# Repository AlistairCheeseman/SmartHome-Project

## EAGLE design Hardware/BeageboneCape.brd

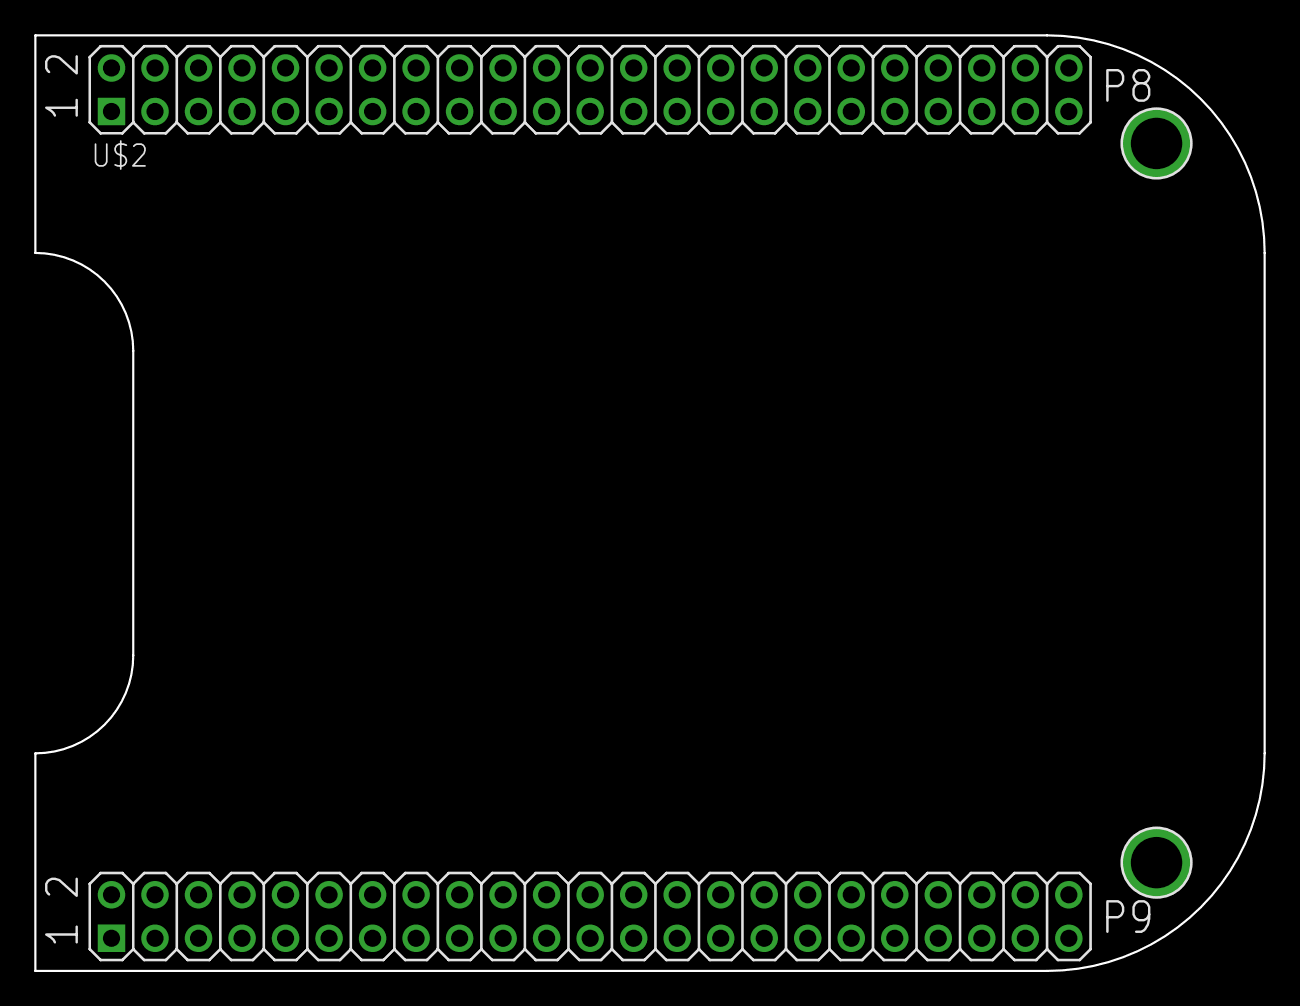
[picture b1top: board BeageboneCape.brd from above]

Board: 2 copper layers, 71.8 x 54.6 mm, 3 parts (0 on the bottom side), 4 nets, no tracks yet.

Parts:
U$2: BEAGLEBONE_OUTLINE; BEAGLEBONE_SHIELD
U$22, U$23: MOUNTINGHOLE3.0THIN; MOUNTINGHOLE_3.0_PLATEDTHIN

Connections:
3.3V: U$2.49, U$2.50
5.0V: U$2.53, U$2.54
GND: U$2.1, U$2.2, U$2.47, U$2.48, U$2.89, U$2.90, U$2.91, U$2.92
VDD_5V: U$2.51, U$2.52

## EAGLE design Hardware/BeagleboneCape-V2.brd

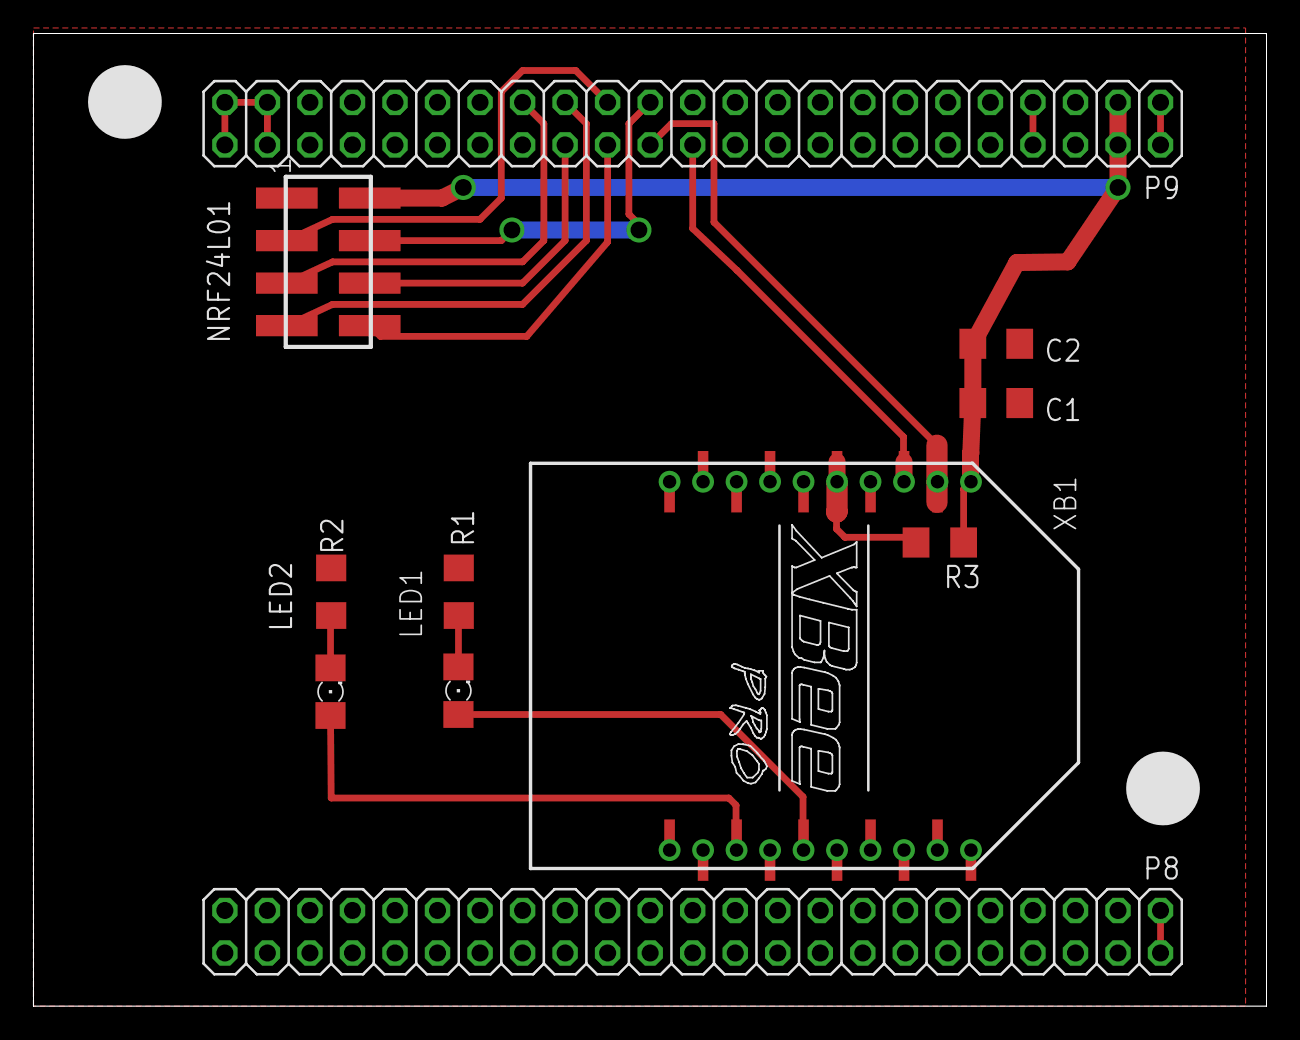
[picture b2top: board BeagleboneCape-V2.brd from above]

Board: 2 copper layers, 73.6 x 58.1 mm, 11 parts (0 on the bottom side), 16 nets.

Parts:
C1: 1u; C1206
C2: 8.2p; C1206
LED1: Assoc; 1206
LED2: ON_SLEEP; 1206
NRF24L01: NRF1; TSM-110-XX-XXX-DV
P8: HEADER1; 2X23
P9: HEADER2; 2X23
R1, R2, R3: 110R; R1206
XB1: XBEE-PRO

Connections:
3.3V: C1.1, C2.1, NRF24L01.2, P9.3, P9.4, R3.1, XB1.1, XB1.1-1
5.0V: P9.7, P9.8
ASSOC: LED1.A, XB1.15, XB1.15-1
BB_RX: P9.26, XB1.2, XB1.2-1
BB_TX: P9.24, XB1.3, XB1.3-1
CE: NRF24L01.3, P9.27
CSN: NRF24L01.4, P9.25
GND: C1.2, C2.2, NRF24L01.1, P8.1, P8.2, P9.1, P9.2, P9.43, P9.44, P9.45, P9.46, R1.1, R2.1, XB1.10, XB1.10-1, XB1.14, XB1.14-1
IRQ: NRF24L01.8, P9.28
MISO: NRF24L01.7, P9.29
MOSI: NRF24L01.6, P9.30
unnamed: LED1.C, R1.2
unnamed: R3.2, XB1.5, XB1.5-1
unnamed: LED2.C, R2.2
ON_SLEEP: LED2.A, XB1.13, XB1.13-1
SCK: NRF24L01.5, P9.31

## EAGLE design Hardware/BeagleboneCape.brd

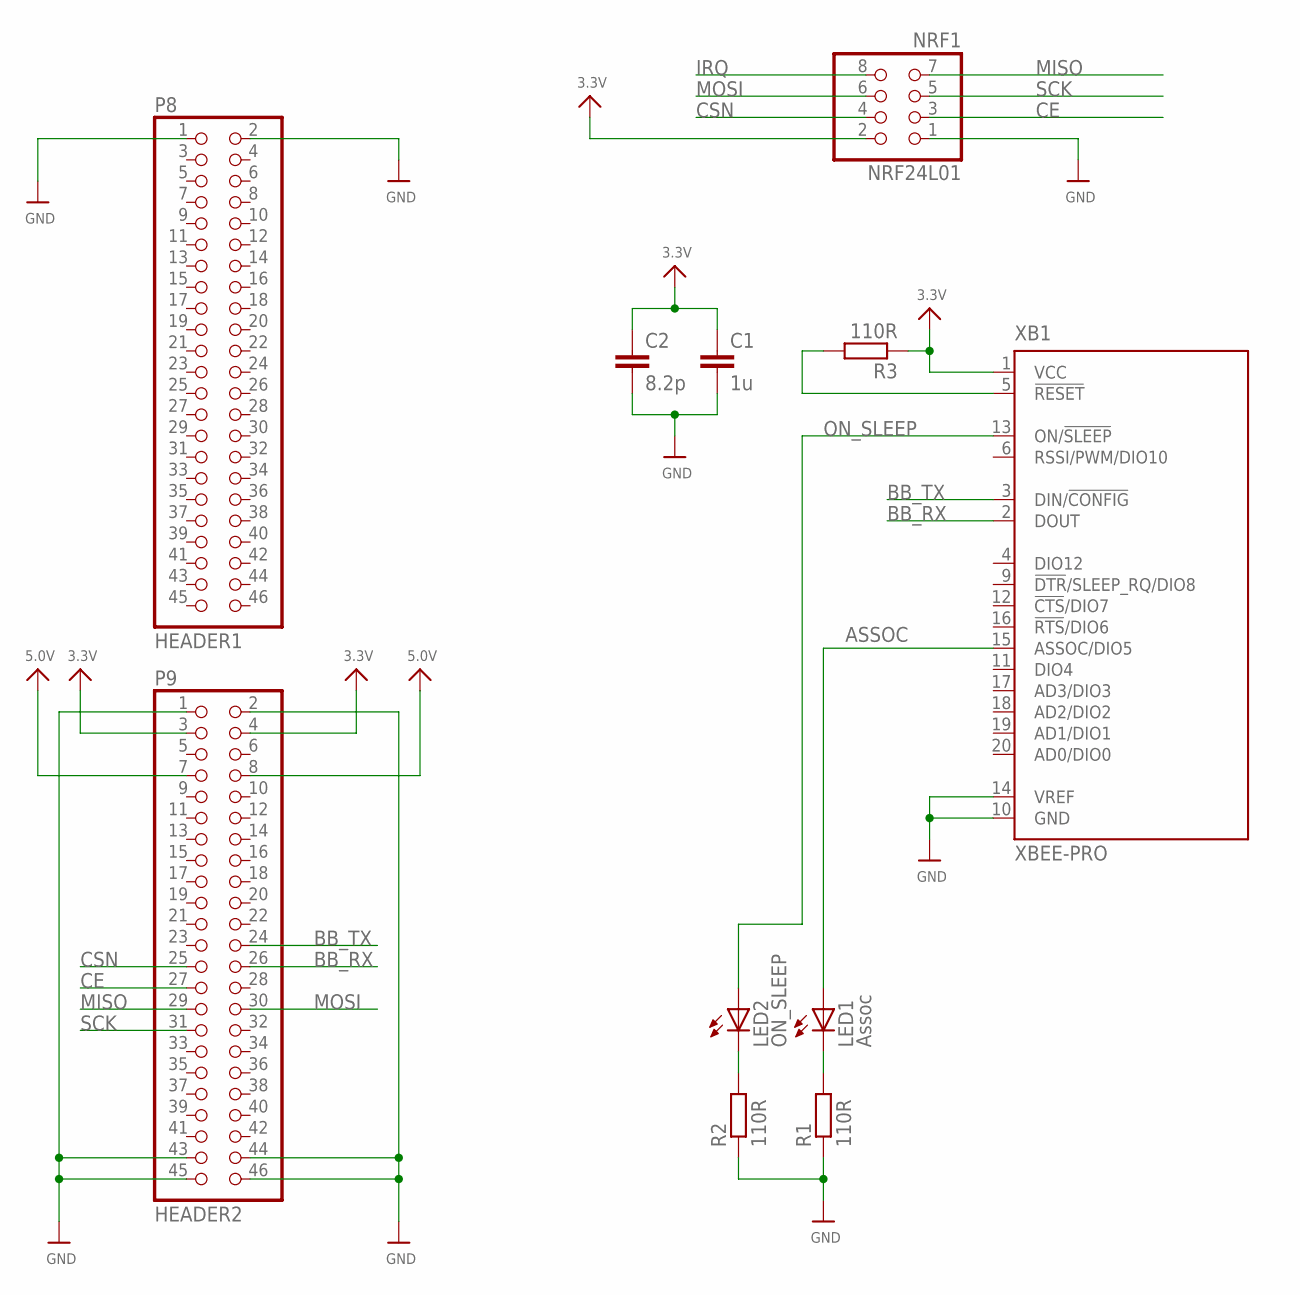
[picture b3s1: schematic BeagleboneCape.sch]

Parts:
C1: 1u; C025-025X050
C2: 8.2p; C025-025X050
LED1: Assoc; LED5MM
LED2: ON_SLEEP; LED5MM
NRF24L01: NRF1; 2X04
P8: HEADER1; 2X23
P9: HEADER2; 2X23
R1, R2, R3: 110R; 0207/7
XB1: XBEE-PRO

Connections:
3.3V: C1.1, C2.1, NRF24L01.2, P9.3, P9.4, R3.1, XB1.1 (VCC)
5.0V: P9.7, P9.8
ASSOC: LED1.A, XB1.15 (ASSOC/DIO5)
BB_RX: P9.26, XB1.2 (DOUT)
BB_TX: P9.24, XB1.3 (DIN/!CONFIG)
CE: NRF24L01.3, P9.27
CSN: NRF24L01.4, P9.25
GND: C1.2, C2.2, NRF24L01.1, P8.1, P8.2, P9.1, P9.2, P9.43, P9.44, P9.45, P9.46, R1.1, R2.1, XB1.10 (GND), XB1.14 (VREF)
IRQ: NRF24L01.8
MISO: NRF24L01.7, P9.29
MOSI: NRF24L01.6, P9.30
unnamed: LED1.K (C), R1.2
unnamed: R3.2, XB1.5 (!RESET)
unnamed: LED2.K (C), R2.2
ON_SLEEP: LED2.A, XB1.13 (ON/!SLEEP)
SCK: NRF24L01.5, P9.31

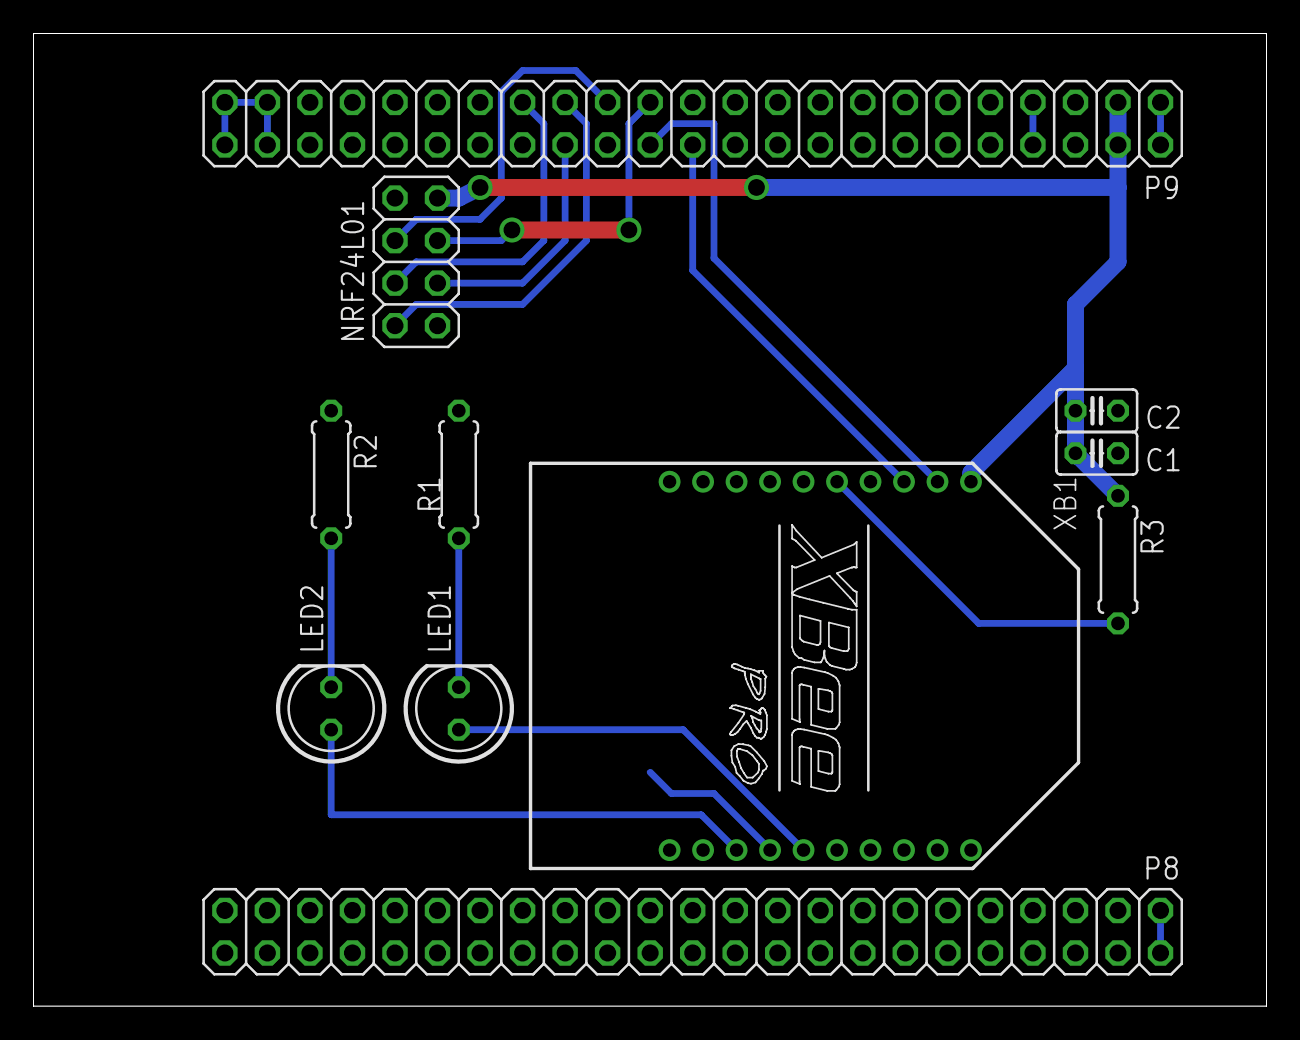
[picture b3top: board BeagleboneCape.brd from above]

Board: 2 copper layers, 73.6 x 58.1 mm, 11 parts (0 on the bottom side), 15 nets.

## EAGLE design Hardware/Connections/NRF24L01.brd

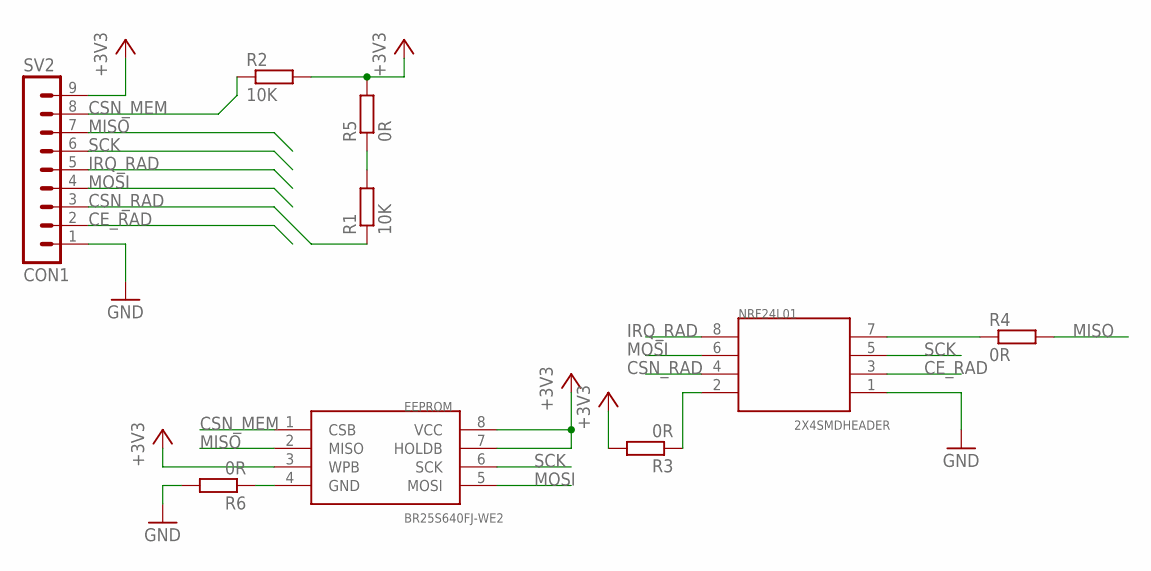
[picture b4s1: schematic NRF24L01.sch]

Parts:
EEPROM: BR25S640FJ-WE2; SO8
NRF24L01: 2X4SMDHEADER; TSM-110-XX-XXX-DV
R1, R2: 10K; R1206
R3, R4, R5, R6: 0R; R1206
SV2: CON1; MA09-1W

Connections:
+3V3: EEPROM.3 (WPB), EEPROM.7 (HOLDB), EEPROM.8 (VCC), R2.2, R3.2, R5.2, SV2.9
CE_RAD: NRF24L01.3, SV2.2
CSN_MEM: EEPROM.1 (CSB), R2.1, SV2.8
CSN_RAD: NRF24L01.4, R1.1, SV2.3
GND: NRF24L01.1, R6.2, SV2.1
IRQ_RAD: NRF24L01.8, SV2.5
MISO: EEPROM.2 (MISO), R4.2, SV2.7
MOSI: EEPROM.5 (MOSI), NRF24L01.6, SV2.4
unnamed: NRF24L01.2, R3.1
unnamed: NRF24L01.7, R4.1
unnamed: R1.2, R5.1
unnamed: EEPROM.4 (GND), R6.1
SCK: EEPROM.6 (SCK), NRF24L01.5, SV2.6

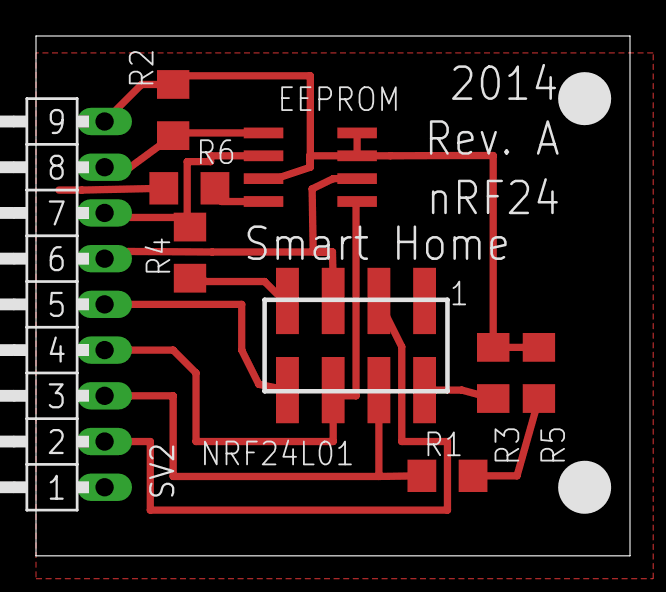
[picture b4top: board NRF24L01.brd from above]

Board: 2 copper layers, 33.0 x 28.9 mm, 9 parts (0 on the bottom side), 13 nets.

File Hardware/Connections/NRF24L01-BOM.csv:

"Qty";"Value";"Device";"Package";"Parts";"Description";"MF";"MPN";"OC_FARNELL";"OC_NEWARK";
"4";"0R";"R-EU_R1206";"R1206";"R3, R4, R5, R6";"RESISTOR, European symbol";"";"";"";"";
"2";"10K";"R-EU_R1206";"R1206";"R1, R2";"RESISTOR, European symbol";"";"";"";"";
"1";"2X4SMDHEADER";"2X4SMDHEADER";"TSM-110-XX-XXX-DV";"U$1";"";"";"";"";"";
"1";"BR25S640FJ-WE2";"BR25S640FJ-WE2";"SO8";"EEPROM";"";"";"";"";"";
"1";"CON1";"MA09-1W";"MA09-1W";"SV2";"PIN HEADER";"";"";"unknown";"unknown";

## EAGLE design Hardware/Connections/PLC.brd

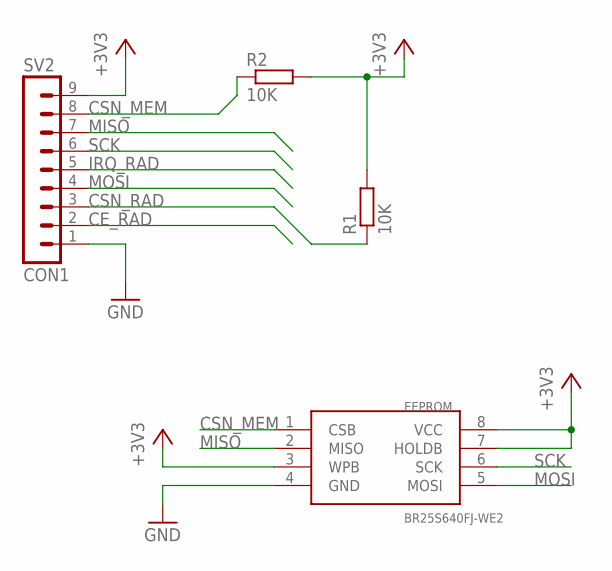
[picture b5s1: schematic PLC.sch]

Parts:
EEPROM: BR25S640FJ-WE2; SO8
R1, R2: 10K; R1206
SV2: CON1; MA09-1W

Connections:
+3V3: EEPROM.3 (WPB), EEPROM.7 (HOLDB), EEPROM.8 (VCC), R1.2, R2.2, SV2.9
CE_RAD: SV2.2
CSN_MEM: EEPROM.1 (CSB), R2.1, SV2.8
CSN_RAD: R1.1, SV2.3
GND: EEPROM.4 (GND), SV2.1
IRQ_RAD: SV2.5
MISO: EEPROM.2 (MISO), SV2.7
MOSI: EEPROM.5 (MOSI), SV2.4
SCK: EEPROM.6 (SCK), SV2.6

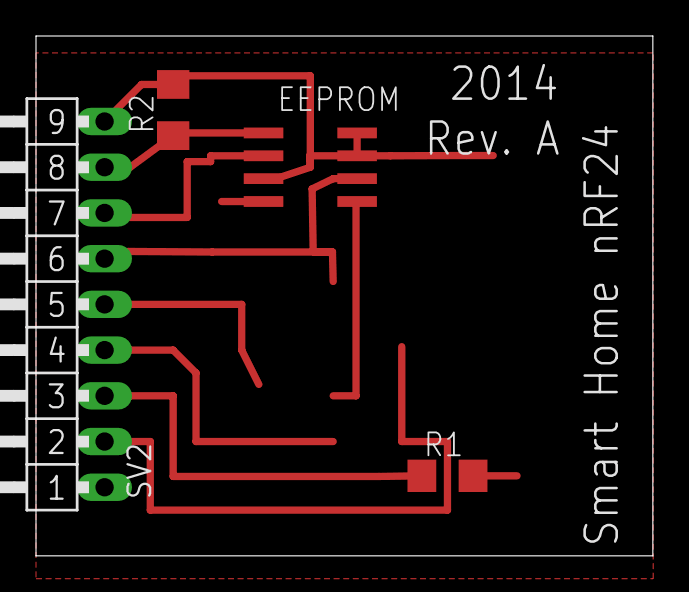
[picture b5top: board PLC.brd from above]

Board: 2 copper layers, 34.3 x 28.9 mm, 4 parts (0 on the bottom side), 7 nets.

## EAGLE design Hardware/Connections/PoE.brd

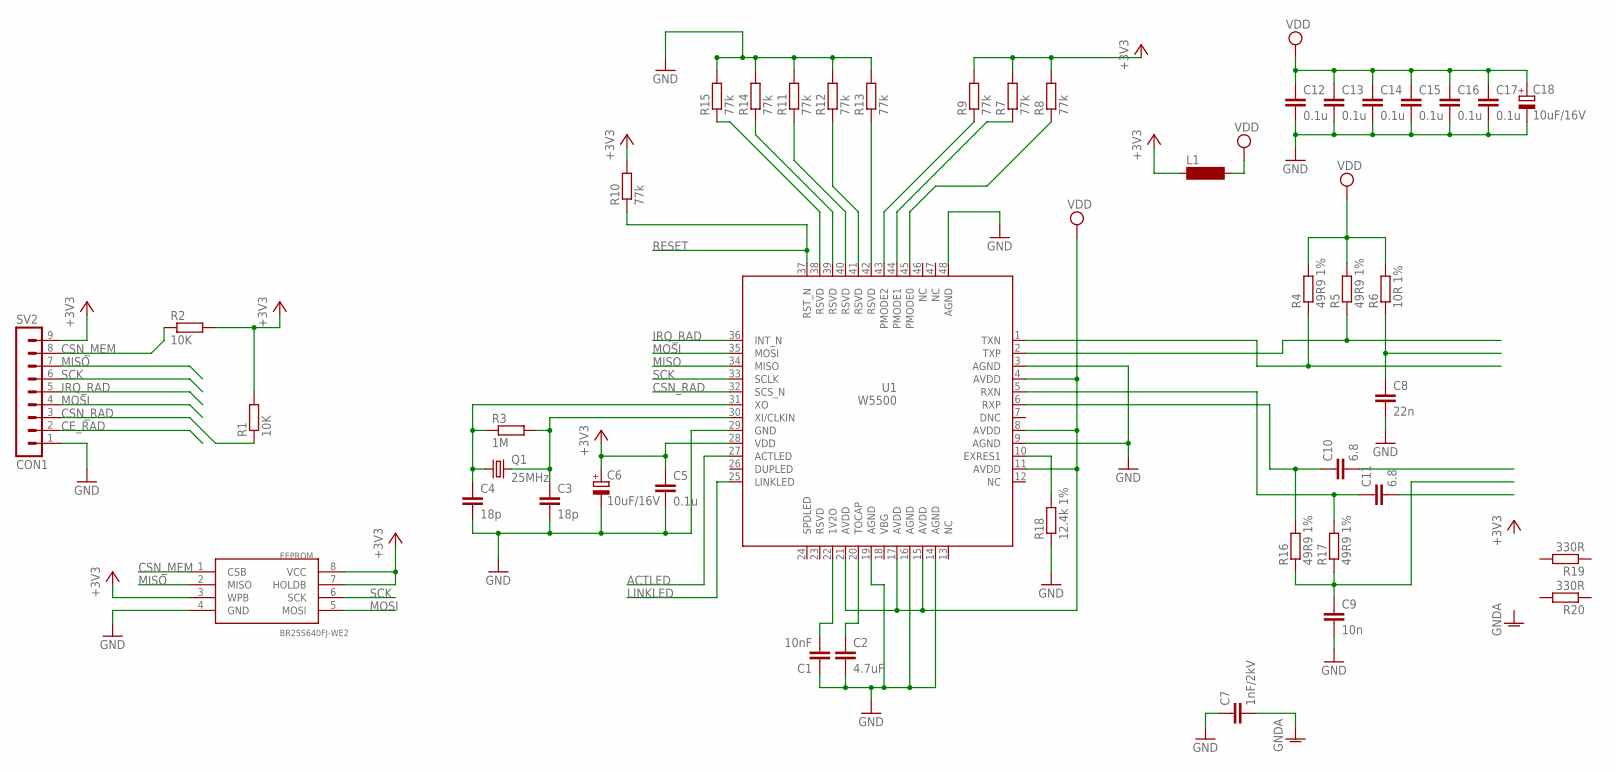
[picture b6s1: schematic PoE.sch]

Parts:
C1: 10nF; C1206
C2: 4.7uF; C1206
C3, C4: 18p; C1206
C5, C12, C13, C14, C15, C16, C17: 0.1u; C1206
C6: 10uF/16V; 153CLV-0505
C7: 1nF/2kV; C1206
C8: 22n; C1206
C9: 10n; C1206
C10, C11: 6.8; C1206
C18: 10uF/16V; 153CLV-0405
EEPROM: BR25S640FJ-WE2; SO8
L1: MS50
Q1: 25MHz; HC49UP
R1, R2: 10K; R1206
R3: 1M; R1206
R4, R5, R16, R17: 49R9 1%; R1206
R6: 10R 1%; R1206
R7, R8, R9, R10, R11, R12, R13, R14, R15: 77k; R1206
R18: 12.4k 1%; R1206
R19, R20: 330R; R1206
SV2: CON1; MA09-1W
U1: W5500

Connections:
+3V3: C5.1, C6.+, EEPROM.3 (WPB), EEPROM.7 (HOLDB), EEPROM.8 (VCC), L1.1, R1.2, R2.2, R7.2, R8.2, R9.2, R10.2, SV2.9, U1.28 (VDD)
ACTLED: U1.27 (ACTLED)
CE_RAD: SV2.2
CSN_MEM: EEPROM.1 (CSB), R2.1, SV2.8
CSN_RAD: R1.1, SV2.3, U1.32 (SCS_N)
GND: C1.1, C2.2, C3.2, C4.2, C5.2, C6.-, C7.1, C8.2, C9.2, C12.2, C13.2, C14.2, C15.2, C16.2, C17.2, C18.-, EEPROM.4 (GND), R11.2, R12.2, R13.2, R14.2, R15.2, R18.1, SV2.1, U1.3 (AGND), U1.9 (AGND), U1.14 (AGND), U1.16 (AGND), U1.19 (AGND), U1.29 (GND), U1.48 (AGND)
GNDA: C7.2
IRQ_RAD: SV2.5, U1.36 (INT_N)
LINKLED: U1.25 (LINKLED)
MISO: EEPROM.2 (MISO), SV2.7, U1.34 (MISO)
MOSI: EEPROM.5 (MOSI), SV2.4, U1.35 (MOSI)
unnamed: R9.1, U1.43 (PMODE2)
unnamed: C1.2, U1.22 (1V2O)
unnamed: C2.1, U1.20 (TOCAP)
unnamed: C4.1, Q1.1, R3.1, U1.31 (XO)
unnamed: C3.1, Q1.2, R3.2, U1.30 (XI/CLKIN)
unnamed: R7.1, U1.44 (PMODE1)
unnamed: C11.1, R17.2, U1.5 (RXN)
unnamed: R8.1, U1.45 (PMODE0)
unnamed: R15.1, U1.38 (RSVD)
unnamed: R14.1, U1.39 (RSVD)
unnamed: R11.1, U1.40 (RSVD)
unnamed: R12.1, U1.41 (RSVD)
unnamed: R13.1, U1.42 (RSVD)
unnamed: R5.1, U1.2 (TXP)
unnamed: C8.1, R6.1
unnamed: R4.1, U1.1 (TXN)
unnamed: C10.1, R16.2, U1.6 (RXP)
unnamed: C9.1, R16.1, R17.1
unnamed: R18.2, U1.10 (EXRES1)
RESET: R10.1, U1.37 (RST_N)
SCK: EEPROM.6 (SCK), SV2.6, U1.33 (SCLK)
VDD: C12.1, C13.1, C14.1, C15.1, C16.1, C17.1, C18.+, L1.2, R4.2, R5.2, R6.2, U1.4 (AVDD), U1.8 (AVDD), U1.11 (AVDD), U1.15 (AVDD), U1.17 (AVDD), U1.21 (AVDD)

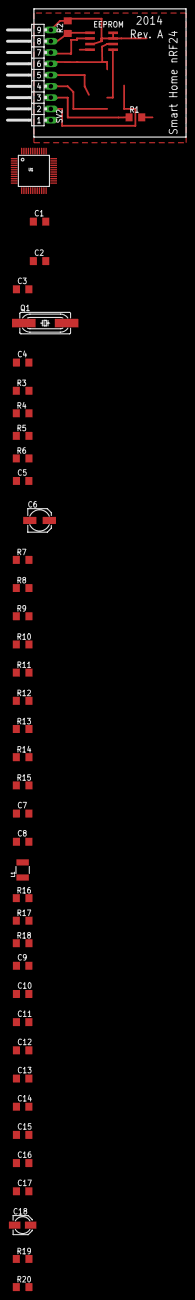
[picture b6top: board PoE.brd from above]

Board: 2 copper layers, 34.3 x 28.9 mm, 43 parts (0 on the bottom side), 29 nets.

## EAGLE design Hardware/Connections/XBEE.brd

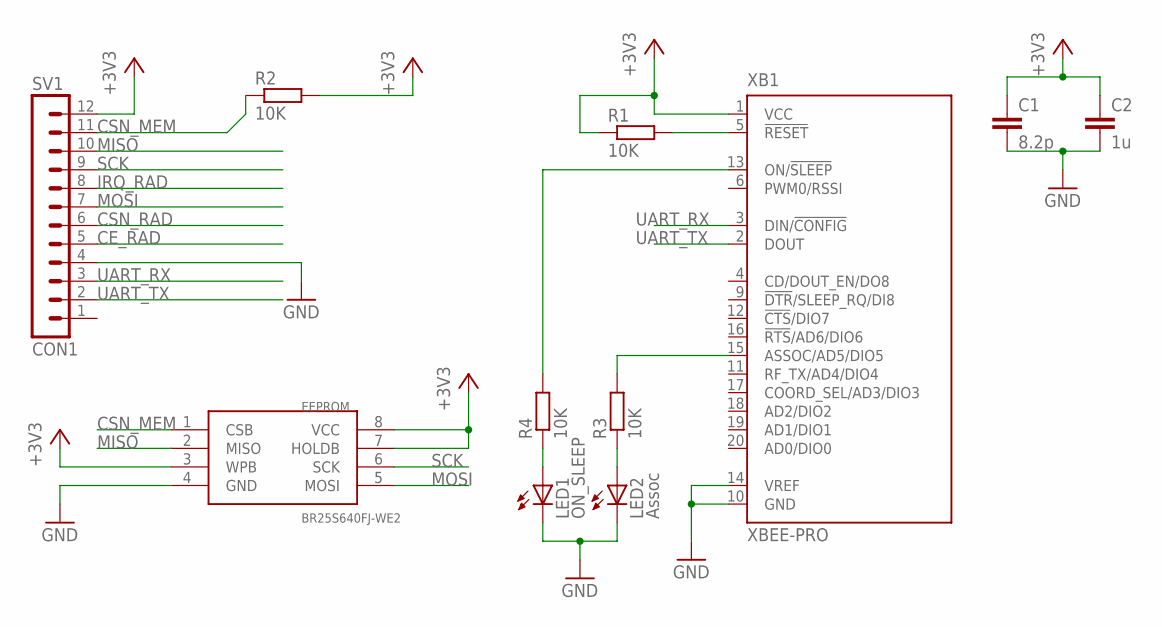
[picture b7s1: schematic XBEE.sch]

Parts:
C1: 8.2p; C1206
C2: 1u; C1206
EEPROM: BR25S640FJ-WE2; SO8
LED1: ON_SLEEP; 1206
LED2: Assoc; 1206
R1, R2, R3, R4: 10K; R1206
SV1: CON1; MA12-1W
XB1: XBEE-PRO

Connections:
+3V3: C1.1, C2.1, EEPROM.3 (WPB), EEPROM.7 (HOLDB), EEPROM.8 (VCC), R1.1, R2.2, SV1.12, XB1.1 (VCC)
CE_RAD: SV1.5
CSN_MEM: EEPROM.1 (CSB), R2.1, SV1.11
CSN_RAD: SV1.6
GND: C1.2, C2.2, EEPROM.4 (GND), LED1.C, LED2.C, SV1.4, XB1.10 (GND), XB1.14 (VREF)
IRQ_RAD: SV1.8
MISO: EEPROM.2 (MISO), SV1.10
MOSI: EEPROM.5 (MOSI), SV1.7
unnamed: R1.2, XB1.5 (!RESET)
unnamed: R4.2, XB1.13 (ON/!SLEEP)
unnamed: R3.2, XB1.15 (ASSOC/AD5/DIO5)
unnamed: LED1.A, R4.1
unnamed: LED2.A, R3.1
SCK: EEPROM.6 (SCK), SV1.9
UART_RX: SV1.3, XB1.3 (DIN/!CONFIG)
UART_TX: SV1.2, XB1.2 (DOUT)

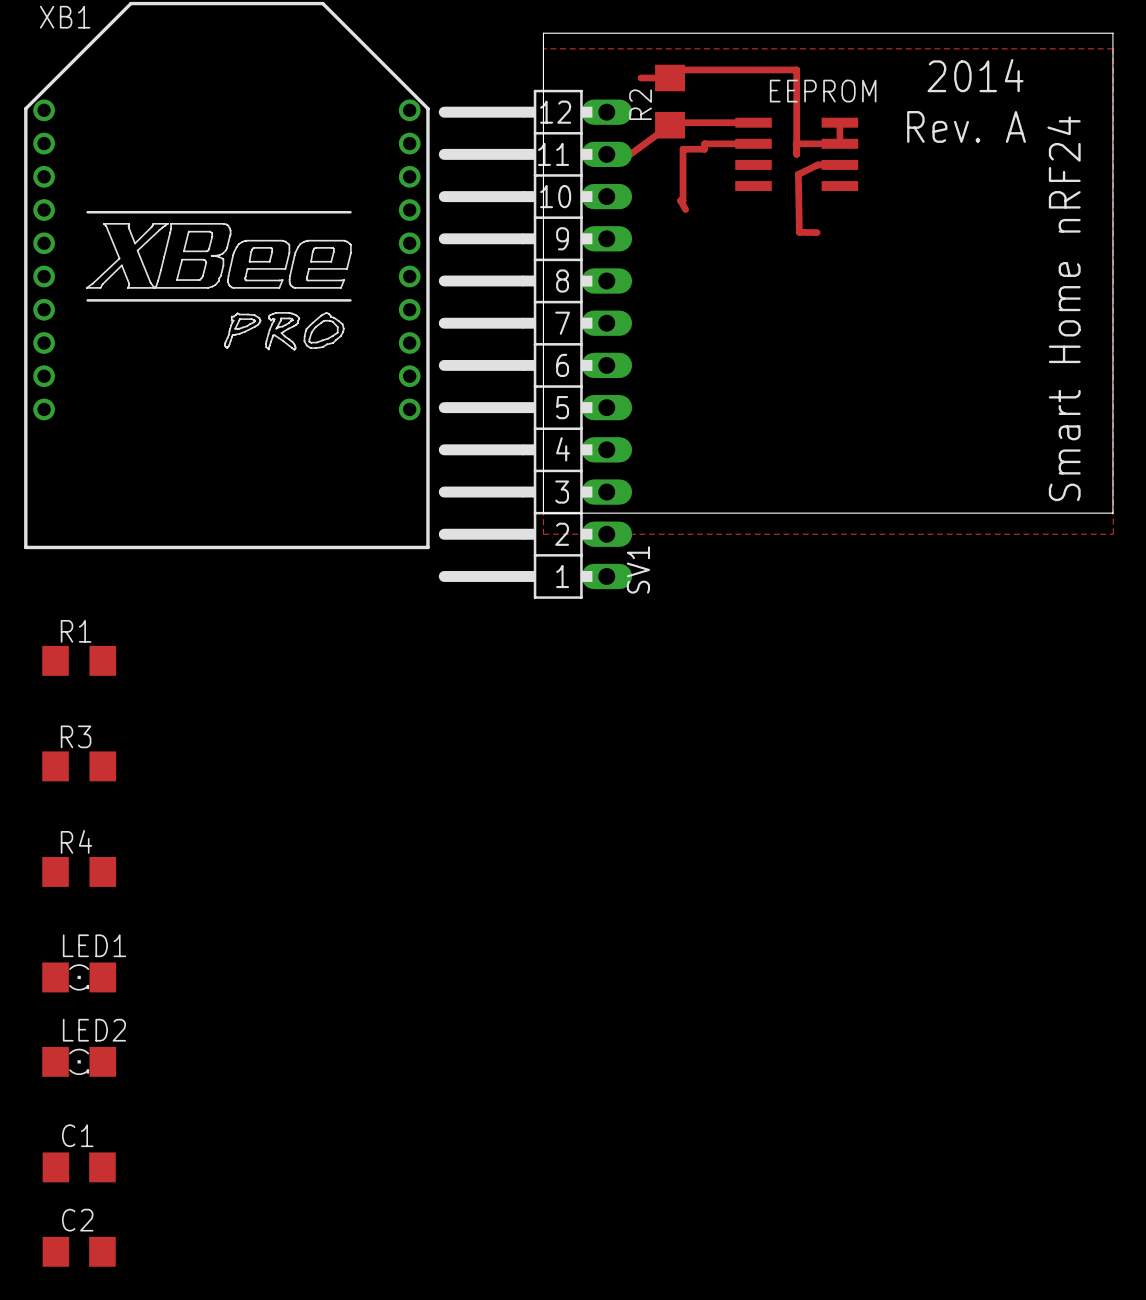
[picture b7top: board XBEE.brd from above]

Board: 2 copper layers, 34.3 x 28.9 mm, 11 parts (0 on the bottom side), 13 nets.
